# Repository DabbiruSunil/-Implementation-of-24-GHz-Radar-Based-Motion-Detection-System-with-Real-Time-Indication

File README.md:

# 📡 24-GHz Radar-Based Motion Detection System with Real-Time Indication

This repository contains the design, development, and testing files for a **24-GHz radar-based motion detection system**, capable of detecting movement with high accuracy using real-time signal processing. The project integrates hardware (custom PCB with a 24-GHz radar module) and software (firmware, MATLAB analysis, and signal processing algorithms) into a complete working system.

---

## 📌 Project Overview

The objective of this project is to build a **precise motion detection system** leveraging a **24-GHz radar sensor**. The radar signals are captured, digitized, and processed in real time to provide immediate feedback when motion is detected.

### Hardware

* Custom PCB designed in **KiCad**.
* Integration of **24-GHz radar module**, **ADC**, **DAC**, and **DMA** for efficient data handling.
* Gerber files provided for fabrication.

### Software

* **Firmware** written in **PSoC Creator** for the Cypress PSoC 5LP microcontroller.
* State machine–based design for efficient real-time processing.
* **MATLAB scripts** for radar data analysis and Discrete Fourier Transform (DFT)–based signal evaluation.

---

## ✨ Features

* **High-frequency motion detection** at 24 GHz.
* **Custom PCB** with modular radar integration.
* **Real-time indication** of detected motion.
* **Efficient data processing pipeline** using DMA and microcontroller firmware.
* **MATLAB support** for offline data visualization and spectral analysis.

---

## 📂 Repository Contents

* **`24GHz-Radar for movement Detection.pptx`** – Presentation of design, implementation, and performance.
* **`Gerber files for PCB.zip`** – Fabrication files for the custom PCB.
* **`KiCad files for PCB.zip`** – Full KiCad project for PCB layout and schematic.
* **`PSoC_project.zip`** – Source code, configuration, and firmware project for PSoC Creator.

---

## 🛠️ Getting Started

### 🔧 Prerequisites

* [KiCad](https://www.kicad.org/) – For PCB design files.
* [PSoC Creator](https://www.cypress.com/products/psoc-creator-integrated-design-environment-ide) – To build and flash firmware onto the PSoC 5LP.
* [MATLAB](https://www.mathworks.com/products/matlab.html) – For radar data analysis and signal processing.
* PCB fabrication service – To manufacture the board from the Gerber files.

### ⚙️ Installation & Usage

#### 1. PCB Design

* Open KiCad project files.
* Review or modify the layout.
* Send **Gerber files** to a PCB manufacturer.

#### 2. Firmware Development

* Open the **PSoC project** in PSoC Creator.
* Compile and program the PSoC 5LP microcontroller.

#### 3. Signal Processing

* Use MATLAB scripts to process captured radar data.
* Perform **DFT analysis** for precise motion detection.

---

## 🧪 Testing & Validation

* Hardware validated through PCB prototypes.
* Firmware tested with real-time motion detection scenarios.
* MATLAB used to visualize motion profiles and confirm radar accuracy.

---

## 🤝 Contributing

Contributions are welcome! To propose improvements:

1. Fork this repository.
2. Create a feature branch.
3. Commit your changes.
4. Submit a pull request with details.

---

## 📜 License

MIT License – see [LICENSE](LICENSE) for details.

**Author:** Sunil Dabbiru

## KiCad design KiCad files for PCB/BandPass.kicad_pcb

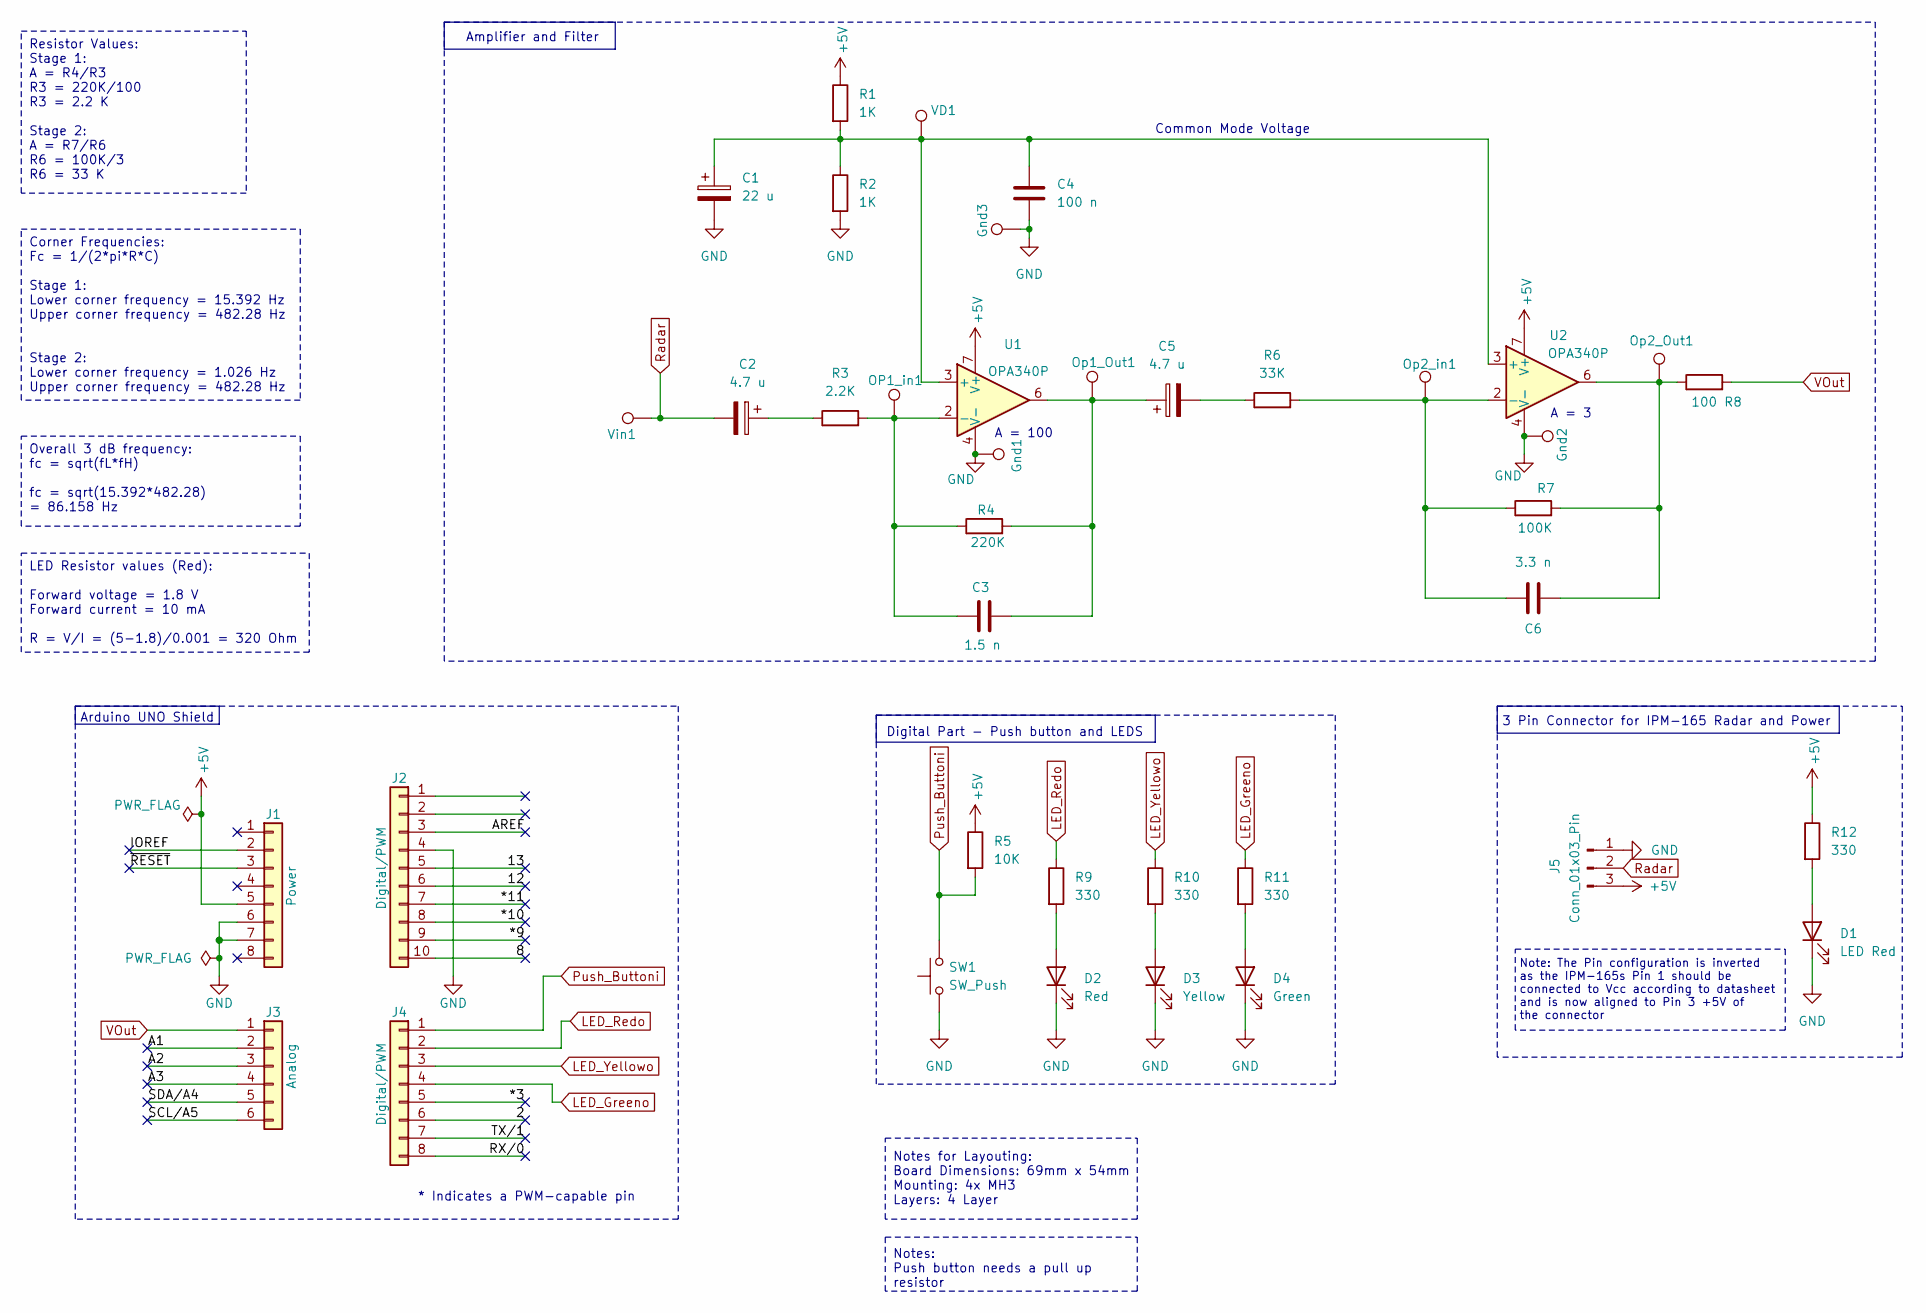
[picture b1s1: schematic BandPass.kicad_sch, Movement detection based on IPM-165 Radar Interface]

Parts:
C1: 22 u; CP_Radial_D5.0mm_P2.00mm
C2, C5: 4.7 u; CP_Radial_D5.0mm_P2.00mm
C3: 1.5 n; C_Rect_L7.2mm_W4.5mm_P5.00mm_FKS2_FKP2_MKS2_MKP2
C4: 100 n; C_Rect_L7.2mm_W3.0mm_P5.00mm_FKS2_FKP2_MKS2_MKP2
C6: 3.3 n; C_Rect_L7.2mm_W4.5mm_P5.00mm_FKS2_FKP2_MKS2_MKP2
D1: LED Red; LED_D5.0mm
D2: Red; LED_D5.0mm
D3: Yellow; LED_D5.0mm
D4: Green; LED_D5.0mm
Gnd1, Gnd2, Gnd3: Gnd; PinHeader_1x01_P2.54mm_Vertical
J1: Power; PinHeader_1x08_P2.54mm_Vertical
J2: Digital/PWM; PinHeader_1x10_P2.54mm_Vertical
J3: Analog; PinHeader_1x06_P2.54mm_Vertical
J4: Digital/PWM; PinHeader_1x08_P2.54mm_Vertical
J5: Conn_01x03_Pin; PinSocket_1x03_P2.54mm_Horizontal
OP1_in1: OP1_In; PinHeader_1x01_P2.54mm_Vertical
Op1_Out1: OP1_Out; PinHeader_1x01_P2.54mm_Vertical
Op2_Out1: OP2_out; PinHeader_1x01_P2.54mm_Vertical
Op2_in1: OP2_In; PinHeader_1x01_P2.54mm_Vertical
R1, R2: 1K; R_Axial_DIN0207_L6.3mm_D2.5mm_P10.16mm_Horizontal
R3: 2.2K; R_Axial_DIN0207_L6.3mm_D2.5mm_P10.16mm_Horizontal
R4: 220K; R_Axial_DIN0207_L6.3mm_D2.5mm_P10.16mm_Horizontal
R5: 10K; R_Axial_DIN0207_L6.3mm_D2.5mm_P10.16mm_Horizontal
R6: 33K; R_Axial_DIN0207_L6.3mm_D2.5mm_P10.16mm_Horizontal
R7: 100K; R_Axial_DIN0207_L6.3mm_D2.5mm_P10.16mm_Horizontal
R8: 100; R_Axial_DIN0207_L6.3mm_D2.5mm_P10.16mm_Horizontal
R9, R10, R11, R12: 330; R_Axial_DIN0207_L6.3mm_D2.5mm_P10.16mm_Horizontal
SW1: SW_Push; SW_PUSH_6mm_H7.3mm
U1, U2: OPA340P; DIP-8_W7.62mm
VD1: Voltage Divider; PinHeader_1x01_P2.54mm_Vertical
Vin1: Vin; PinHeader_1x01_P2.54mm_Vertical

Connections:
+5V: J1.5, J5.3, R1.1, R5.1, R12.1, U1.7 (V+), U2.7 (V+)
/2: J4.6
/8: J2.10
/12: J2.6
/13: J2.5
/*3: J4.5
/*9: J2.9
/*10: J2.8
/*11: J2.7
/A1: J3.2
/A2: J3.3
/A3: J3.4
/AREF: J2.3
/IOREF: J1.2
/RX/0: J4.8
/SCL/A5: J3.6
/SDA/A4: J3.5
/TX/1: J4.7
/~RESET: J1.3
GND: C1.2, C4.2, D1.1 (K), D2.1 (K), D3.1 (K), D4.1 (K), Gnd1.1, Gnd2.1, Gnd3.1, J1.6, J1.7, J2.4, J5.1, R2.2, SW1.1, U1.4 (V-), U2.4 (V-)
LED_Greeno: J4.4, R11.1
LED_Redo: J4.2, R9.1
LED_Yellowo: J4.3, R10.1
unnamed: C2.1, R3.1
unnamed: C3.2, C5.1, Op1_Out1.1, R4.2, U1.6
unnamed: C5.2, R6.1
unnamed: C6.2, Op2_Out1.1, R7.2, R8.1, U2.6
unnamed: D1.2 (A), R12.2
unnamed: D2.2 (A), R9.2
unnamed: D3.2 (A), R10.2
unnamed: D4.2 (A), R11.2
unnamed: C1.1, C4.1, R1.2, R2.1, U1.3 (+), U2.3 (+), VD1.1
unnamed: C3.1, OP1_in1.1, R3.2, R4.1, U1.2 (-)
unnamed: C6.1, Op2_in1.1, R6.2, R7.1, U2.2 (-)
Push_Buttoni: J4.1, R5.2, SW1.2
Radar: C2.2, J5.2, Vin1.1
VOut: J3.1, R8.2

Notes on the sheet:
Corner Frequencies: Fc = 1/(2*pi*R*C) Stage 1: Lower corner frequency = 15.392 Hz Upper corner frequency = 482.28 Hz Stage 2: Lower corner frequency = 1.026 Hz Upper corner frequency = 482.28 Hz
Resistor Values: Stage 1: A = R4/R3 R3 = 220K/100 R3 = 2.2 K Stage 2: A = R7/R6 R6 = 100K/3 R6 = 33 K
Overall 3 dB frequency: fc = sqrt(fL*fH) fc = sqrt(15.392*482.28) = 86.158 Hz
LED Resistor values (Red): Forward voltage = 1.8 V Forward current = 10 mA R = V/I = (5-1.8)/0.001 = 320 Ohm
Notes for Layouting: Board Dimensions: 69mm x 54mm Mounting: 4x MH3 Layers: 4 Layer
3 Pin Connector for IPM-165 Radar and Power
Digital Part - Push button and LEDS
Notes: Push button needs a pull up resistor
Arduino UNO Shield
Amplifier and Filter
* Indicates a PWM-capable pin
Common Mode Voltage
A = 100
Note: The Pin configuration is inverted as the IPM-165s Pin 1 should be connected to Vcc according to datasheet and is now aligned to Pin 3 +5V of the connector
A = 3

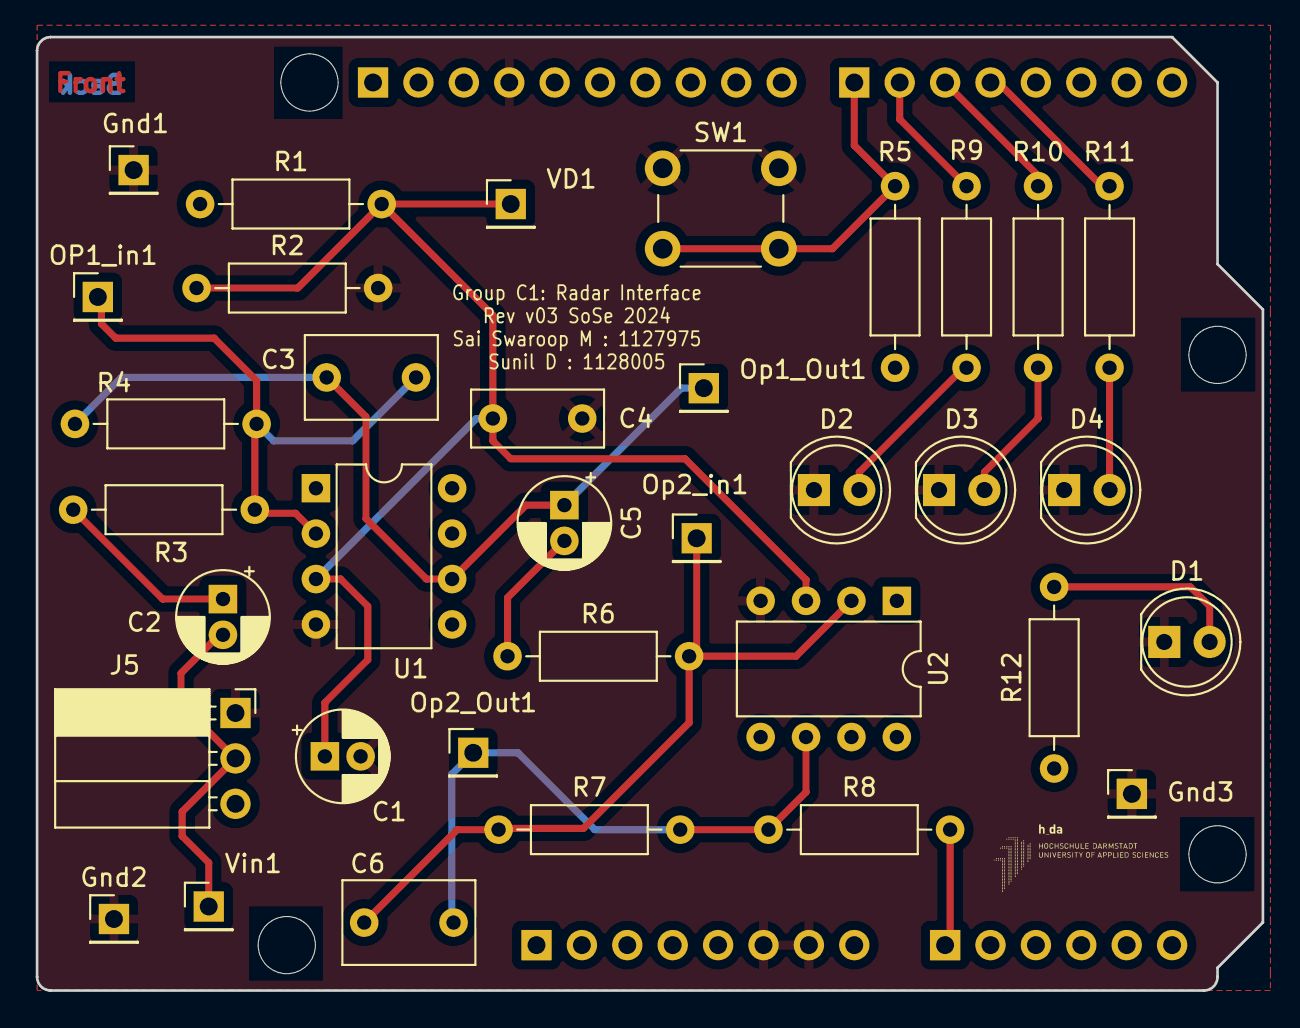
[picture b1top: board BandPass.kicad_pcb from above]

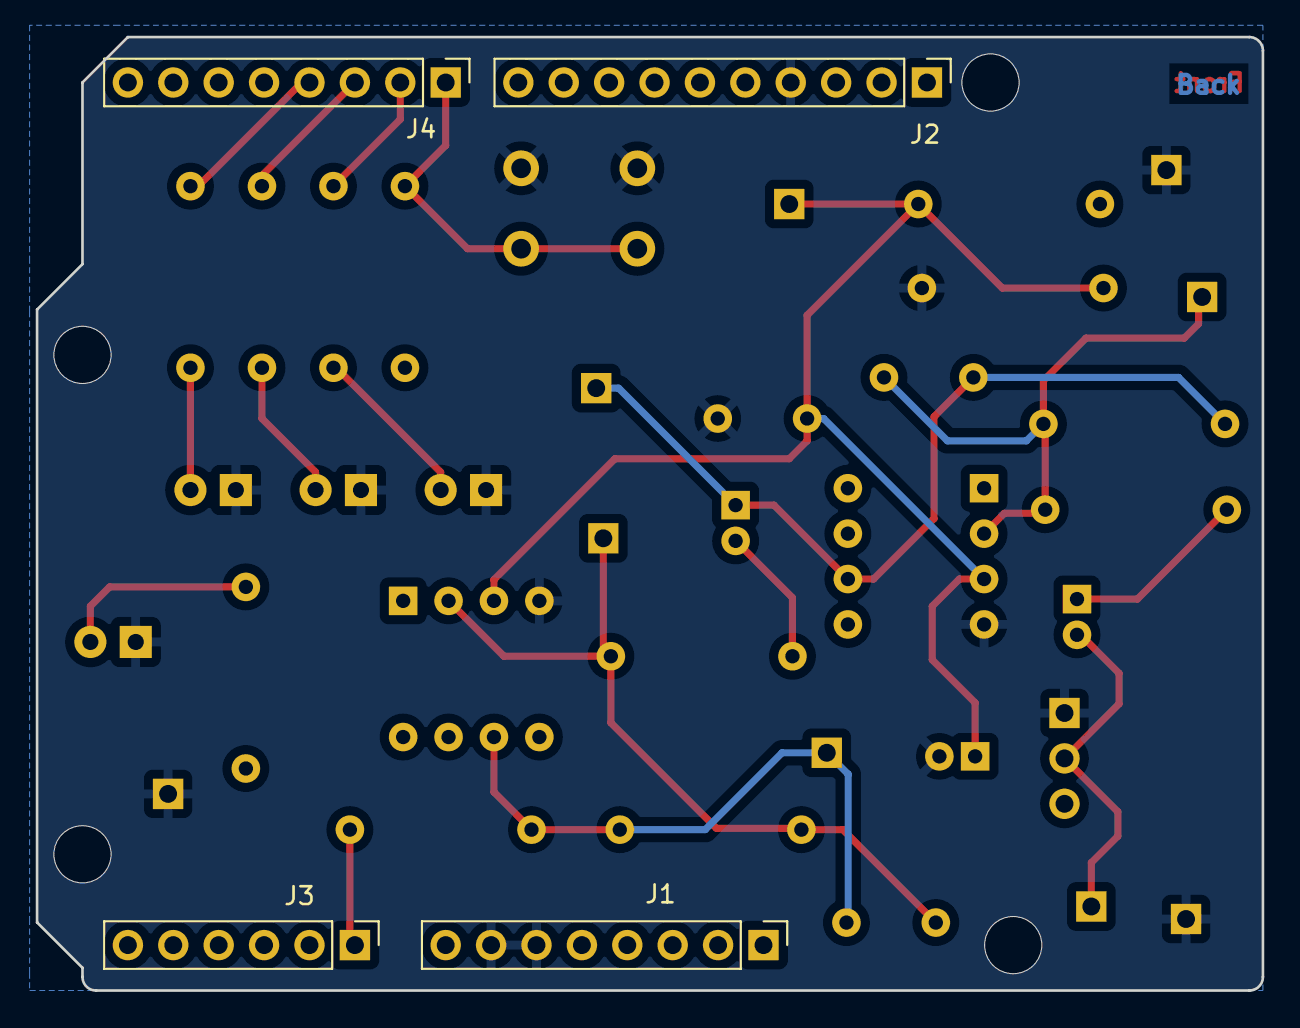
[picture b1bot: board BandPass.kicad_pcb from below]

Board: 4 copper layers, 68.6 x 53.3 mm, 43 parts (4 on the bottom side), 19 nets.

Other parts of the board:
MH1, MH2, MH3, MH4: MountingHole_3.2mm

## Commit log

2024-08-24 Add PSoC project files
2024-08-24 Add KiCAD files to repository
2024-08-24 Add Gerber fiiles to repository
2024-08-24 Add README files to repository
